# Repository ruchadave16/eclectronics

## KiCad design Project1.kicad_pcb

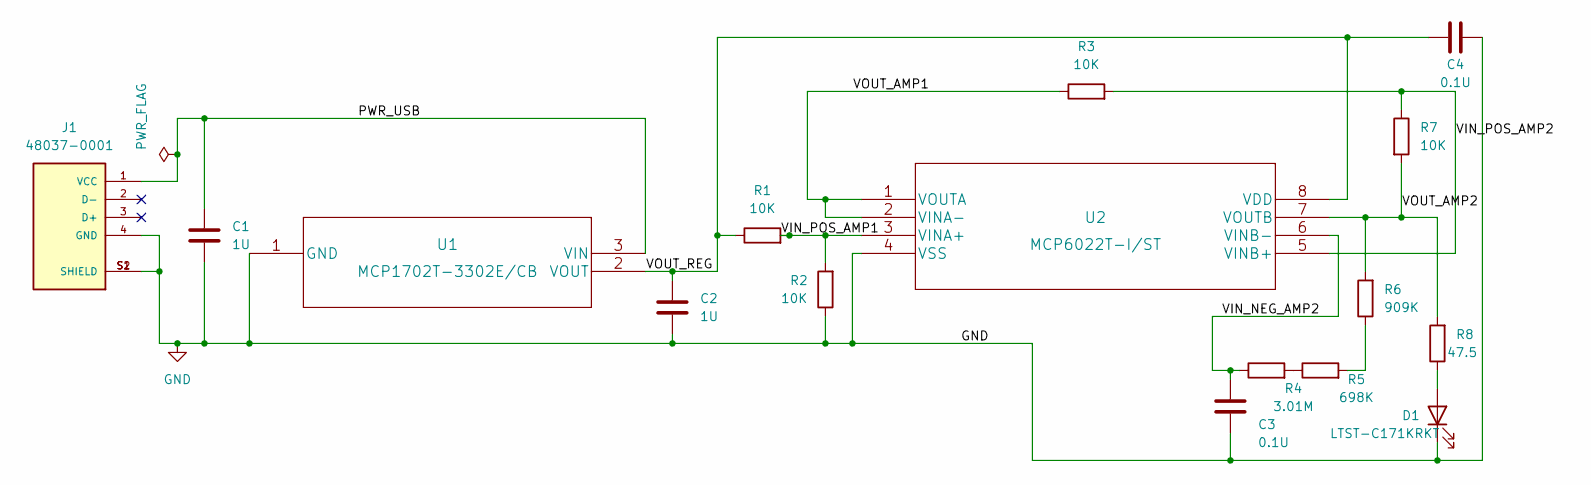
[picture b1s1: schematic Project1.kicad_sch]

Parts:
C1, C2: 1U; C_0603_1608Metric_Pad1.08x0.95mm_HandSolder
C3, C4: 0.1U; C_0603_1608Metric_Pad1.08x0.95mm_HandSolder
D1: LTST-C171KRKT; LED_0805_2012Metric_Pad1.15x1.40mm_HandSolder
J1: 48037-0001; MOLEX_48037-0001; PARTREV D
R1, R2, R3, R7: 10K; R_0603_1608Metric_Pad0.98x0.95mm_HandSolder
R4: 3.01M; R_0603_1608Metric_Pad0.98x0.95mm_HandSolder
R5: 698K; R_0603_1608Metric_Pad0.98x0.95mm_HandSolder
R6: 909K; R_0603_1608Metric_Pad0.98x0.95mm_HandSolder
R8: 47.5; R_0603_1608Metric_Pad0.98x0.95mm_HandSolder
U1: MCP1702T-3302E/CB; SOT-23A_MC_MCH
U2: MCP6022T-I/ST; TSSOP8_MC_MCH

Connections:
/PWR_USB: C1.2, J1.1 (VCC), U1.3 (VIN)
/VIN_NEG_AMP2: C3.2, R4.1, U2.6 (VINB-)
/VIN_POS_AMP1: R1.2, R2.2, U2.3 (VINA+)
/VIN_POS_AMP2: R3.2, R7.1, U2.5 (VINB+)
/VOUT_AMP1: R3.1, U2.1 (VOUTA), U2.2 (VINA-)
/VOUT_AMP2: R6.2, R7.2, R8.2, U2.7 (VOUTB)
/VOUT_REG: C2.2, C4.1, R1.1, U1.2 (VOUT), U2.8 (VDD)
GND: C1.1, C2.1, C3.1, C4.2, D1.1 (K), J1.4 (GND), J1.S1 (SHIELD), J1.S2 (SHIELD), R2.1, U1.1 (GND), U2.4 (VSS)
unnamed: D1.2 (A), R8.1
unnamed: R4.2, R5.1
unnamed: R5.2, R6.1

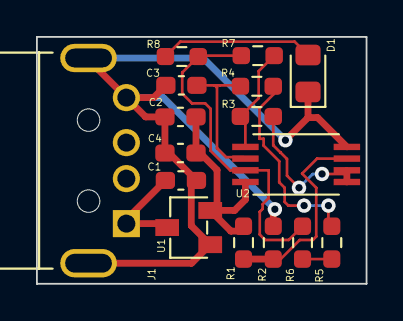
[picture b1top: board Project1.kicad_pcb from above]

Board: 2 copper layers, 18.3 x 13.7 mm, 16 parts (0 on the bottom side), 11 nets.

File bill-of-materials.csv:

Source:,C:\Users\rdave\OneDrive - Olin College of Engineering\Year2\eclectronics\Project1.kicad_sch,,,,,,,,,
Date:,9/16/2022 1:46,,,,,,,,,
Tool:,Eeschema (6.0.7),,,,,,,,,
Generator:,C:\Program Files\KiCad\6.0\bin\scripting\plugins/bom_csv_grouped_by_value.py,,,,,,,,,
Component Count:,16,,,,,,,,,
,,,,,,,,,,
Individual Components:,,,,,,,,,,
,,,,,,,,,,
Item,Qty,Reference(s),Value,LibPart,Footprint,Datasheet,MANUFACTURER,MAXIMUM_PACKAGE_HEIGHT,PARTREV,STANDARD
,,C1,1U,Device:C,Capacitor_SMD:C_0603_1608Metric_Pad1.08x0.95mm_HandSolder,~,,,,
,,C2,1U,Device:C,Capacitor_SMD:C_0603_1608Metric_Pad1.08x0.95mm_HandSolder,~,,,,
,,C3,0.1U,Device:C,Capacitor_SMD:C_0603_1608Metric_Pad1.08x0.95mm_HandSolder,~,,,,
,,C4,0.1U,Device:C,Capacitor_SMD:C_0603_1608Metric_Pad1.08x0.95mm_HandSolder,~,,,,
,,D1,LTST-C171KRKT,Device:LED,LED_SMD:LED_0805_2012Metric_Pad1.15x1.40mm_HandSolder,~,,,,
,,J1,48037-0001,48037-0001:48037-0001,48037-0001:MOLEX_48037-0001,,Molex,4.6mm,D,Manufacturer Recommendations
,,R1,10K,Device:R,Resistor_SMD:R_0603_1608Metric_Pad0.98x0.95mm_HandSolder,~,,,,
,,R2,10K,Device:R,Resistor_SMD:R_0603_1608Metric_Pad0.98x0.95mm_HandSolder,~,,,,
,,R3,10K,Device:R,Resistor_SMD:R_0603_1608Metric_Pad0.98x0.95mm_HandSolder,~,,,,
,,R4,3.01M,Device:R,Resistor_SMD:R_0603_1608Metric_Pad0.98x0.95mm_HandSolder,~,,,,
,,R5,698K,Device:R,Resistor_SMD:R_0603_1608Metric_Pad0.98x0.95mm_HandSolder,~,,,,
,,R6,909K,Device:R,Resistor_SMD:R_0603_1608Metric_Pad0.98x0.95mm_HandSolder,~,,,,
,,R7,10K,Device:R,Resistor_SMD:R_0603_1608Metric_Pad0.98x0.95mm_HandSolder,~,,,,
,,R8,47.5,Device:R,Resistor_SMD:R_0603_1608Metric_Pad0.98x0.95mm_HandSolder,~,,,,
,,U1,MCP1702T-3302E/CB,MCP1702T-3302E{slash}CB:MCP1702T-3302E{slash}CB,MCP1702T-3302E/CB:MCP1702T-3302E&slash_CB,,,,,
,,U2,MCP6022T-I/ST,MCP6022T-I{slash}ST:MCP6022T-I{slash}ST,MCP6022T-I/ST:MCP6022T-I&slash_ST,,,,,
,,,,,,,,,,
,,,,,,,,,,
,,,,,,,,,,
Collated Components:,,,,,,,,,,
,,,,,,,,,,
Item,Qty,Reference(s),Value,LibPart,Footprint,Datasheet,MANUFACTURER,MAXIMUM_PACKAGE_HEIGHT,PARTREV,STANDARD
1,2,"C1, C2",1U,Device:C,Capacitor_SMD:C_0603_1608Metric_Pad1.08x0.95mm_HandSolder,~,,,,
2,2,"C3, C4",0.1U,Device:C,Capacitor_SMD:C_0603_1608Metric_Pad1.08x0.95mm_HandSolder,~,,,,
3,1,D1,LTST-C171KRKT,Device:LED,LED_SMD:LED_0805_2012Metric_Pad1.15x1.40mm_HandSolder,~,,,,
4,1,J1,48037-0001,48037-0001:48037-0001,48037-0001:MOLEX_48037-0001,,Molex,4.6mm,D,Manufacturer Recommendations
5,4,"R1, R2, R3, R7",10K,Device:R,Resistor_SMD:R_0603_1608Metric_Pad0.98x0.95mm_HandSolder,~,,,,
6,1,R4,3.01M,Device:R,Resistor_SMD:R_0603_1608Metric_Pad0.98x0.95mm_HandSolder,~,,,,
7,1,R5,698K,Device:R,Resistor_SMD:R_0603_1608Metric_Pad0.98x0.95mm_HandSolder,~,,,,
8,1,R6,909K,Device:R,Resistor_SMD:R_0603_1608Metric_Pad0.98x0.95mm_HandSolder,~,,,,
9,1,R8,47.5,Device:R,Resistor_SMD:R_0603_1608Metric_Pad0.98x0.95mm_HandSolder,~,,,,
10,1,U1,MCP1702T-3302E/CB,MCP1702T-3302E{slash}CB:MCP1702T-3302E{slash}CB,MCP1702T-3302E/CB:MCP1702T-3302E&slash_CB,,,,,
11,1,U2,MCP6022T-I/ST,MCP6022T-I{slash}ST:MCP6022T-I{slash}ST,MCP6022T-I/ST:MCP6022T-I&slash_ST,,,,,

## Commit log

2022-09-15 Add footprints
2022-09-15 Add KiCad Designs
2022-09-15 Add missing KiCad file
2022-09-16 Fix footprint for USB Connector
2022-09-16 Add report and necessary files
2022-09-16 Add Bill of Materials
2022-09-16 Add repo to pdf
2022-09-16 Rename files to be more clear
2022-09-16 Fix schematic errors
2022-09-16 Fix trace errors in pcb
2022-09-16 Final changes to report done
2022-09-16 Reupload Report
2022-09-16 Add report final
2022-09-16 Change version of report
2022-09-16 Add final copy of report

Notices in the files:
parts and their libraries:
Copyright 2021 Accelerated Designs. All rights reserved.
